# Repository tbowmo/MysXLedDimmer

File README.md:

## MysXLedDimmer

2 channel FET add-on for MysX connector (PWM channels)

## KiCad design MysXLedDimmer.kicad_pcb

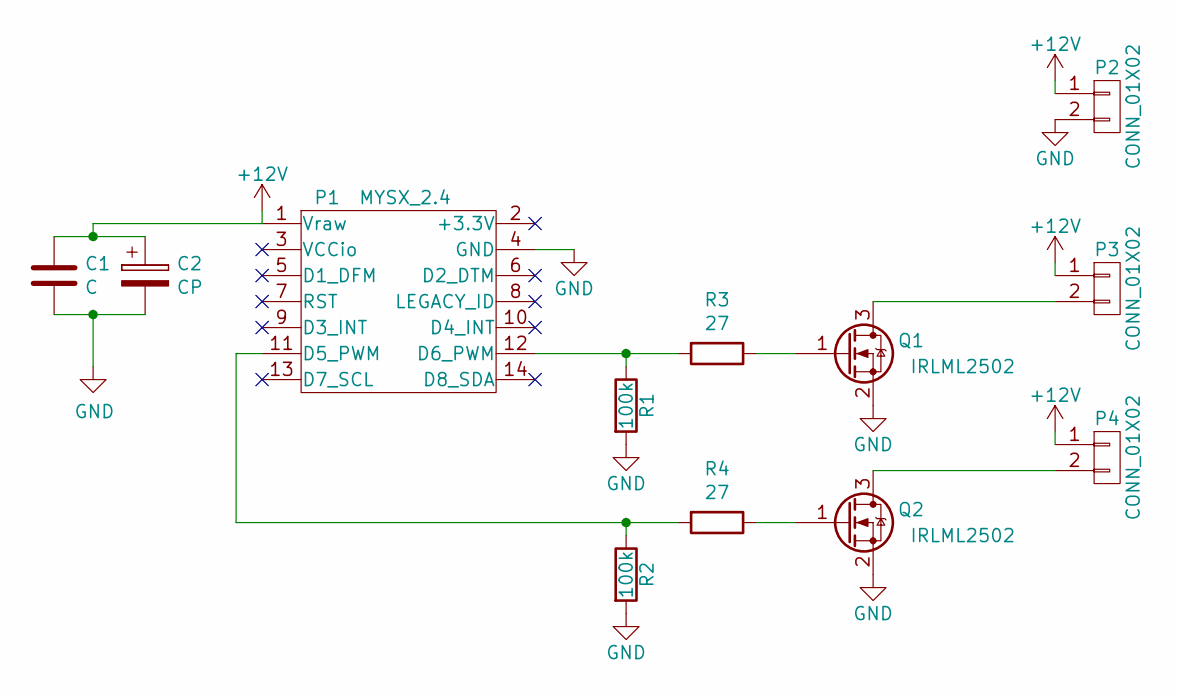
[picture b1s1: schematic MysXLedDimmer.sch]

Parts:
C1: C; C_0805_HandSoldering
C2: CP; C_0805_HandSoldering
P1: MYSX_2.4; MYSX_1.3
P2, P3, P4: CONN_01X02; TerminalBlock2.54mmx2-kcswalter
Q1, Q2: IRLML2502; SOT-23_Handsoldering
R1, R2: 100k; R_0805_HandSoldering
R3, R4: 27; R_0805_HandSoldering

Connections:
+12V: C1.1, C2.1, P1.1 (Vraw), P2.1, P3.1, P4.1
GND: C1.2, C2.2, P1.4 (GND), P2.2, Q1.2 (S), Q2.2 (S), R1.2, R2.2
unnamed: P1.11 (D5_PWM), R2.1, R4.2
unnamed: P1.12 (D6_PWM), R1.1, R3.2
unnamed: P3.2, Q1.3 (D)
unnamed: P4.2, Q2.3 (D)
unnamed: Q1.1 (G), R3.1
unnamed: Q2.1 (G), R4.1

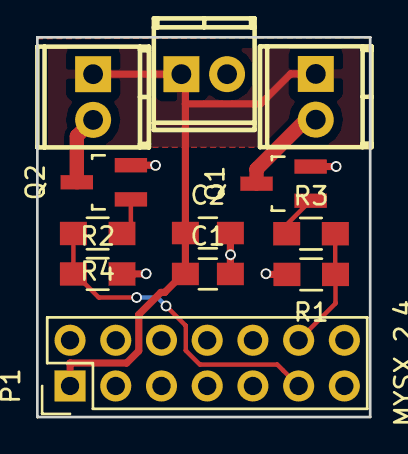
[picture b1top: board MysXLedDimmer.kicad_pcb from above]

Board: 2 copper layers, 18.5 x 21.1 mm, 12 parts (0 on the bottom side), 8 nets.

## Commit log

2017-02-18 Changed to use IRLML2502 in sot23
2017-02-22 Updated gerbers, preparing for pcb ordering
